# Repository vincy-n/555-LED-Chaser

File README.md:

# 555-LED-Chaser
A Butterfly-Shaped LED chaser which blinks 10 LEDs in a variable speed sequence

Schematic:

PCB + 3D Preview:

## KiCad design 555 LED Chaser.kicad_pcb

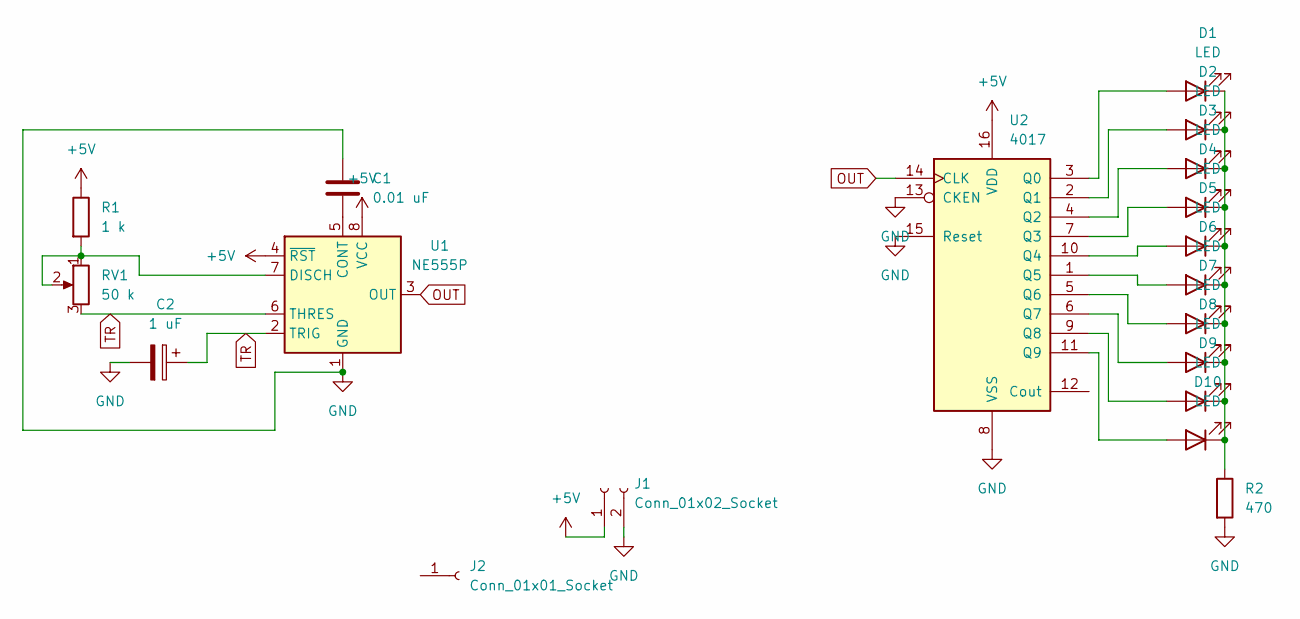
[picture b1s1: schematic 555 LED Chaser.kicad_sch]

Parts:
C1: 0.01 uF; C_Disc_D7.5mm_W2.5mm_P5.00mm
C2: 1 uF; CP_Radial_D5.0mm_P2.00mm
D1, D2, D3, D4, D5, D6, D7, D8, D9, D10: LED; LED_D3.0mm
J1: Conn_01x02_Socket; PinHeader_1x02_P2.54mm_Vertical
J2: Conn_01x01_Socket; PinHeader_1x01_P2.54mm_Vertical
R1: 1 k; R_Axial_DIN0207_L6.3mm_D2.5mm_P7.62mm_Horizontal
R2: 470; R_Axial_DIN0207_L6.3mm_D2.5mm_P7.62mm_Horizontal
RV1: 50 k; Potentiometer_Vishay_T93YA_Vertical
U1: NE555P; DIP-8_W7.62mm
U2: 4017; N16

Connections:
+5V: J1.1, R1.1, U1.4 (~RST), U1.8 (VCC), U2.16 (VDD)
GND: C1.1, C2.2, J1.2, R2.2, U1.1 (GND), U2.8 (VSS), U2.13 (CKEN), U2.15 (Reset)
unnamed: D1.2 (A), U2.3 (Q0)
unnamed: D1.1 (K), D2.1 (K), D3.1 (K), D4.1 (K), D5.1 (K), D6.1 (K), D7.1 (K), D8.1 (K), D9.1 (K), D10.1 (K), R2.1
unnamed: D2.2 (A), U2.2 (Q1)
unnamed: D3.2 (A), U2.4 (Q2)
unnamed: D4.2 (A), U2.7 (Q3)
unnamed: D5.2 (A), U2.10 (Q4)
unnamed: D6.2 (A), U2.1 (Q5)
unnamed: D7.2 (A), U2.5 (Q6)
unnamed: D8.2 (A), U2.6 (Q7)
unnamed: D9.2 (A), U2.9 (Q8)
unnamed: D10.2 (A), U2.11 (Q9)
unnamed: C1.2, U1.5 (CONT)
unnamed: R1.2, RV1.1, RV1.2, U1.7 (DISCH)
OUT: U1.3 (OUT), U2.14 (CLK)
TR: C2.1, RV1.3, U1.2 (TRIG), U1.6 (THRES)

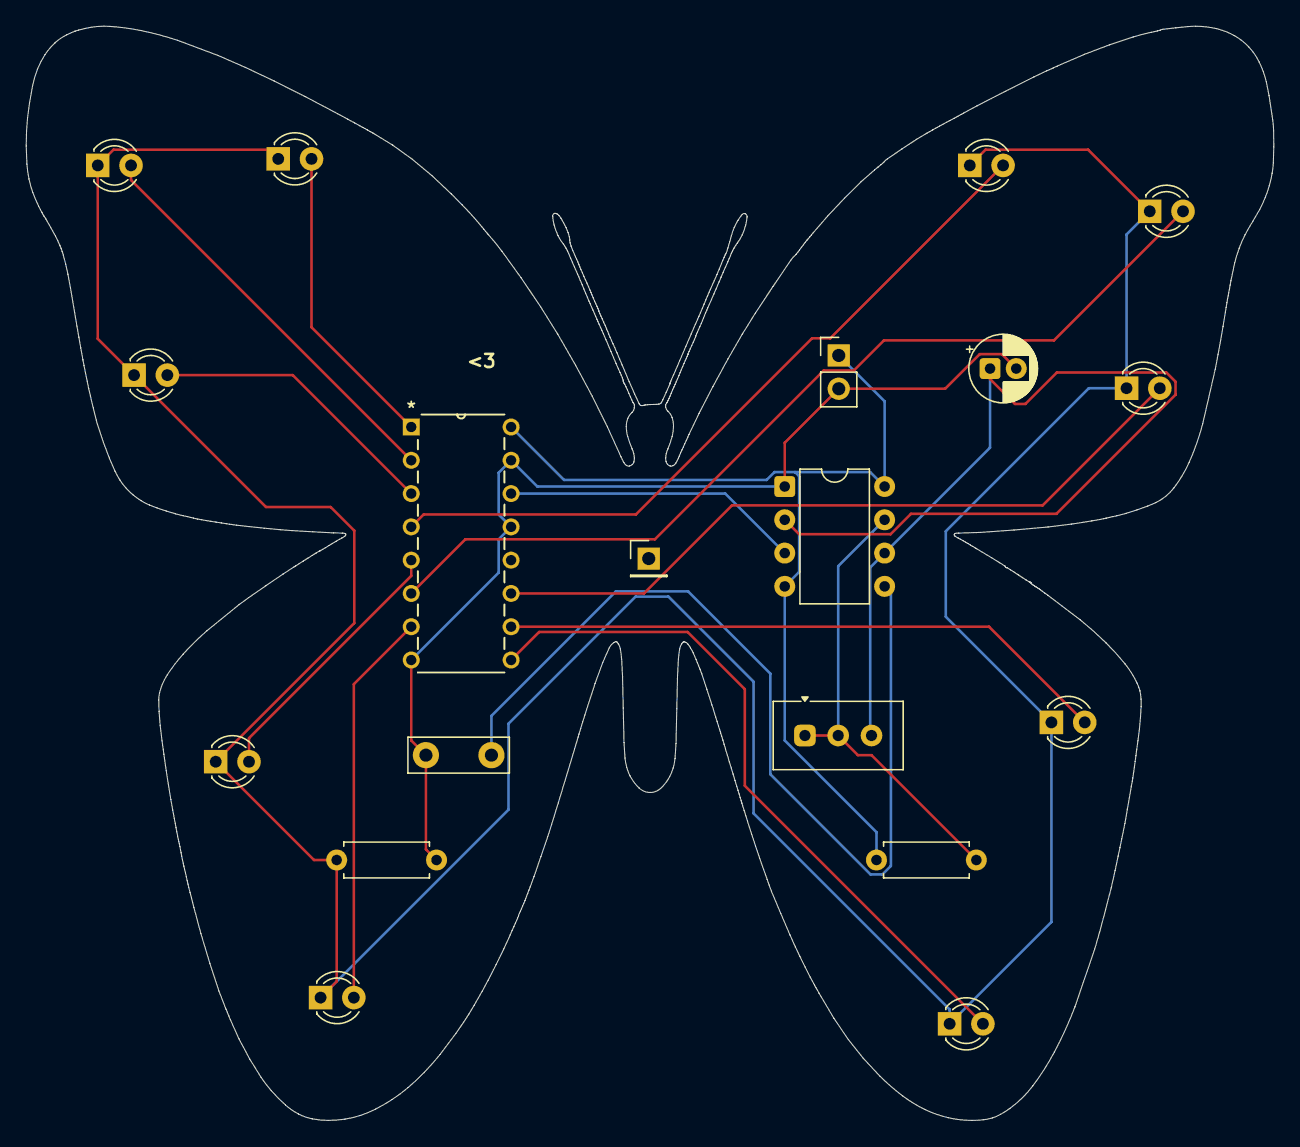
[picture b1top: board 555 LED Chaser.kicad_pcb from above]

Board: 2 copper layers, 95.2 x 83.5 mm, 19 parts (0 on the bottom side), 17 nets.

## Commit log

2026-04-06 Enhance README with schematic and PCB previews
    Added schematic and PCB 3D preview images to README.
